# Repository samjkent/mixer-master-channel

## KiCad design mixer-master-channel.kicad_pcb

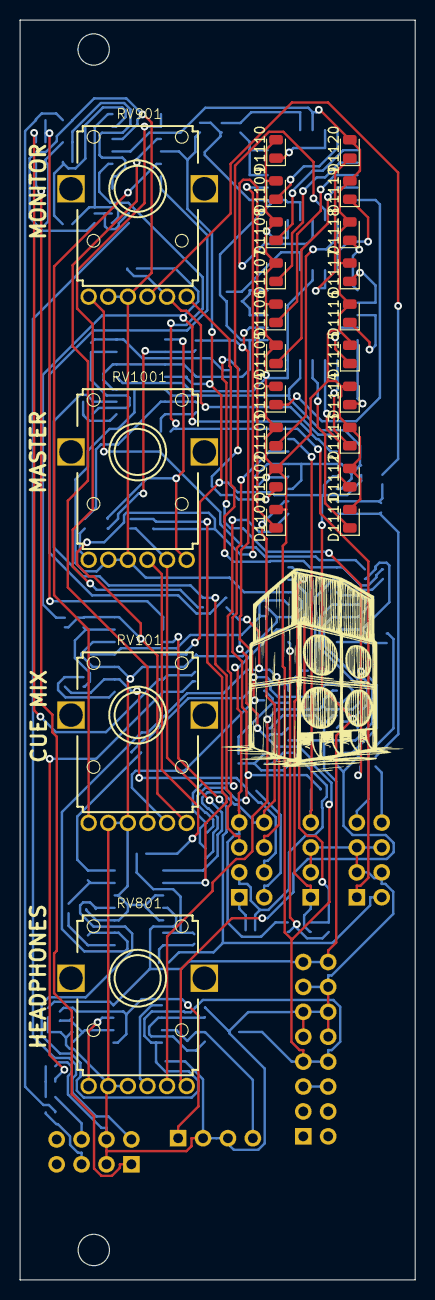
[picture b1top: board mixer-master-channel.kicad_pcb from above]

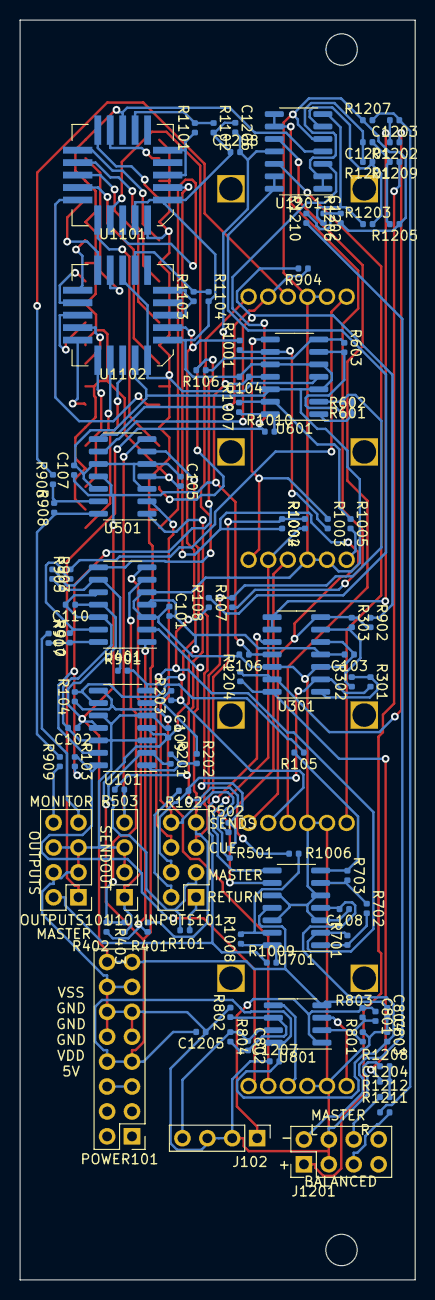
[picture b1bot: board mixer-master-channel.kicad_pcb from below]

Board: 2 copper layers, 40.3 x 128.5 mm, 128 parts (104 on the bottom side), 106 nets.

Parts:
C101, C102, C103, C104, C105, C106, C107, C108, C109, C110, C803, C804: 0.1u; C_0402_1005Metric
C801, C802: 47p; C_0402_1005Metric
C1201, C1202, C1203, C1204, C1207, C1208: 10u; C_0402_1005Metric
C1205, C1206: 1u; C_0402_1005Metric
D1101, D1102, D1103, D1104, D1105, D1106, D1107, D1108, D1109, D1110, D1111, D1112, D1113, D1114, D1115, D1116, D1117, D1118, D1119, D1120: LED; LED_0805_2012Metric
INPUTS101: Conn_02x04_Counter_Clockwise; PinHeader_2x04_P2.54mm_Vertical
J101: SEND_OUT; PinHeader_1x04_P2.54mm_Vertical
J102: HEADPHONE; PinHeader_1x04_P2.54mm_Vertical
J1201: BALANCED; PinHeader_2x04_P2.54mm_Vertical
OUTPUTS101: Conn_02x04_Counter_Clockwise; PinHeader_2x04_P2.54mm_Vertical
POWER101: Conn_02x08_Counter_Clockwise; PinHeader_2x08_P2.54mm_Vertical
R101, R102, R103, R104, R105, R106, R107, R108, R202, R203, R302, R303, R402, R403, R502, R503, R602, R603, R702, R703, R901, R902, R905, R906, R907, R908, R909, R910, R1001, R1002, R1005, R1006, R1007, R1008, R1009, R1010, R1201, R1202, R1203, R1204, R1205, R1206, R1207, R1208: 10k; R_0402_1005Metric
R201, R301, R401, R501, R601, R701: 10K; R_0402_1005Metric
R801, R802, R1209, R1210, R1211, R1212: 1k; R_0402_1005Metric
R803, R804: 6k; R_0402_1005Metric
R903, R904, R1003, R1004: 50k; R_0402_1005Metric
R1101, R1103: 1.2k; R_0402_1005Metric
R1102, R1104: 3.8k; R_0402_1005Metric
RV101: CUEMIX; PTV112
RV801: HEADPHONE_VOL; PTV112
RV901, RV1001: GAIN; PTV112
U101, U301, U401, U501, U601, U701, U1201: TL074; SOIC-14_3.9x8.7mm_P1.27mm
U801: OPA1688; SOIC-8_3.9x4.9mm_P1.27mm
U1101, U1102: LM3916; PLCC-20-LongPads

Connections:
+5V: POWER101.5, POWER101.6
/Sheet60B047F7/LN: J1201.2, R1210.1
/Sheet60B047F7/LP: J1201.1, R1209.1
/Sheet60B047F7/RN: J1201.6, R1212.1
/Sheet60B047F7/RP: J1201.5, R1211.1
/Sheet60360677/IN_L: R103.1, RV801.3, U101.14
/Sheet60360677/IN_R: R104.1, RV801.6, U101.8
/Sheet60360677/OUT_L: C801.1, J102.1, R803.1, U801.1
/Sheet60360677/OUT_R: C802.1, J102.4, R804.1, U801.7
/sheet6034CADD/SUM: J101.1, R403.1, U401.7
/sheet6034CADE/SUM: J101.4, R503.1, U501.7
/sheet6034D121/SUM: R106.1, R603.1, U601.7
/sheet6034D122/SUM: R105.2, R703.1, U701.7
BUS_L: INPUTS101.3, R101.1, R201.2, U101.2
BUS_R: INPUTS101.4, R102.1, R301.2, U301.2
CUE_L: INPUTS101.5, R107.2, R601.2, U601.2
CUE_R: INPUTS101.6, R108.1, R701.2, U701.2
GND: C101.1, C102.2, C103.1, C104.2, C105.1, C106.2, C107.2, C108.1, C109.1, C110.2, C803.1, C804.2, C1205.1, C1206.1, C1207.1, C1208.1, J101.2, J101.3, J102.2, J102.3, J1201.3, J1201.4, OUTPUTS101.3, OUTPUTS101.4, OUTPUTS101.5, OUTPUTS101.6, POWER101.9, POWER101.10, POWER101.11, POWER101.12, POWER101.13, POWER101.14, R801.2, R802.2, R1102.2, R1104.2, R1205.1, R1206.1, R1207.1, R1208.1, RV101.1, RV101.4, RV801.1, RV801.4, RV901.1, RV901.4, RV1001.1, RV1001.4, U101.3, U101.5, U101.10, U101.12, U301.3, U301.5, U301.12, U401.3, U401.5, U401.10, U401.12, U501.3, U501.5, U501.10, U501.12, U601.3, U601.5, U601.10, U601.12, U701.3, U701.5, U701.10, U701.12, U1101.2, U1101.4, U1102.2, U1102.4, U1201.5
MASTER_L: OUTPUTS101.1, R1010.1, U1201.3
MASTER_R: OUTPUTS101.2, R1009.1, U301.10
MONITOR_L: OUTPUTS101.7, R910.1
MONITOR_R: OUTPUTS101.8, R909.1
unnamed: C801.2, R801.1, R803.2, U801.2
unnamed: C802.2, R802.1, R804.2, U801.6
unnamed: C1201.1, R1205.2, R1209.2
unnamed: C1201.2, R1201.2, U1201.1, U1201.2
unnamed: C1202.1, R1206.2, R1210.2
unnamed: C1202.2, R1203.1, U1201.7
unnamed: C1203.1, R1207.2, R1211.2
unnamed: C1203.2, R1202.2, U301.8, U301.9
unnamed: C1204.1, R1208.2, R1212.2
unnamed: C1204.2, R1204.1, U301.14
unnamed: D1101.1, U1101.1
unnamed: D1102.1, U1101.20
unnamed: D1103.1, U1101.19
unnamed: D1104.1, U1101.18
unnamed: D1105.1, U1101.17
unnamed: D1106.1, U1101.16
unnamed: D1107.1, U1101.15
unnamed: D1108.1, U1101.14
unnamed: D1109.1, U1101.13
unnamed: D1110.1, U1101.12
unnamed: D1111.1, U1102.1
unnamed: D1112.1, U1102.20
unnamed: D1113.1, U1102.19
unnamed: D1114.1, U1102.18
unnamed: D1115.1, U1102.17
unnamed: D1116.1, U1102.16
unnamed: D1117.1, U1102.15
unnamed: D1118.1, U1102.14
unnamed: D1119.1, U1102.13
unnamed: D1120.1, U1102.12
unnamed: R103.2, R106.2, U101.13
unnamed: R104.2, R105.1, U101.9
unnamed: R107.1, U1201.8, U1201.9
unnamed: R108.2, U1201.13, U1201.14
unnamed: R201.1, R202.2, U101.1
unnamed: R202.1, R203.2, U101.6
unnamed: R301.1, R302.2, U301.1
unnamed: R302.1, R303.2, U301.6
unnamed: R401.1, R402.2, U401.1
unnamed: R402.1, R403.2, U401.6
unnamed: R501.1, R502.2, U501.1
unnamed: R502.1, R503.2, U501.6
unnamed: R601.1, R602.2, U601.1
unnamed: R602.1, R603.2, U601.6
unnamed: R701.1, R702.2, U701.1
unnamed: R702.1, R703.2, U701.6
unnamed: R901.1, R903.2, U401.9
unnamed: R902.1, R904.2, U501.9
unnamed: R903.1, RV901.3, U401.8
unnamed: R904.1, RV901.6, U501.8
unnamed: R905.1, R907.2, U401.13
unnamed: R905.2, RV901.2
unnamed: R906.1, R908.2, U501.13
unnamed: R906.2, RV901.5
unnamed: R907.1, R910.2, U401.14
unnamed: R908.1, R909.2, U501.14
unnamed: R1001.1, R1003.2, U601.9
unnamed: R1002.1, R1004.2, U701.9
unnamed: R1003.1, RV1001.3, U601.8
unnamed: R1004.1, RV1001.6, U701.8
unnamed: R1005.1, R1007.2, U601.13
unnamed: R1005.2, RV1001.2
unnamed: R1006.1, R1008.2, U701.13
unnamed: R1006.2, RV1001.5
unnamed: R1007.1, R1010.2, U601.14
unnamed: R1008.1, R1009.2, U701.14
unnamed: R1101.1, U1101.6, U1101.8
unnamed: R1101.2, R1102.1, U1101.10
unnamed: R1103.1, U1102.6, U1102.8
unnamed: R1103.2, R1104.1, U1102.10
unnamed: R1201.1, R1203.2, U1201.6
unnamed: R1202.1, R1204.2, U301.13
unnamed: RV101.2, U1201.12
unnamed: RV101.5, U1201.10
unnamed: RV801.2, U801.3
unnamed: RV801.5, U801.5
RETURN_L: INPUTS101.1, R101.2
RETURN_R: INPUTS101.2, R102.2
SEND_L: INPUTS101.7, R401.2, U401.2
SEND_R: INPUTS101.8, R501.2, U501.2
SUMMED_L: R203.1, R901.2, R1001.2, RV101.6, U101.7, U1102.5
SUMMED_R: R303.1, R902.2, R1002.2, RV101.3, U301.7, U1101.5
VDD: C101.2, C103.2, C105.2, C108.2, C109.2, C803.2, C1205.2, C1207.2, D1101.2, D1102.2, D1103.2, D1104.2, D1105.2, D1106.2, D1107.2, D1108.2, D1109.2, D1110.2, D1111.2, D1112.2, D1113.2, D1114.2, D1115.2, D1116.2, D1117.2, D1118.2, D1119.2, D1120.2, POWER101.7, POWER101.8, U101.4, U301.4, U401.4, U501.4, U601.4, U701.4, U801.8, U1101.3, U1101.11, U1102.3, U1102.11, U1201.4
VSS: C102.1, C104.1, C106.1, C107.1, C110.1, C804.1, C1206.2, C1208.2, POWER101.15, POWER101.16, U101.11, U301.11, U401.11, U501.11, U601.11, U701.11, U801.4, U1201.11

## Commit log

2021-07-28 Added buffer to CUEMIX
